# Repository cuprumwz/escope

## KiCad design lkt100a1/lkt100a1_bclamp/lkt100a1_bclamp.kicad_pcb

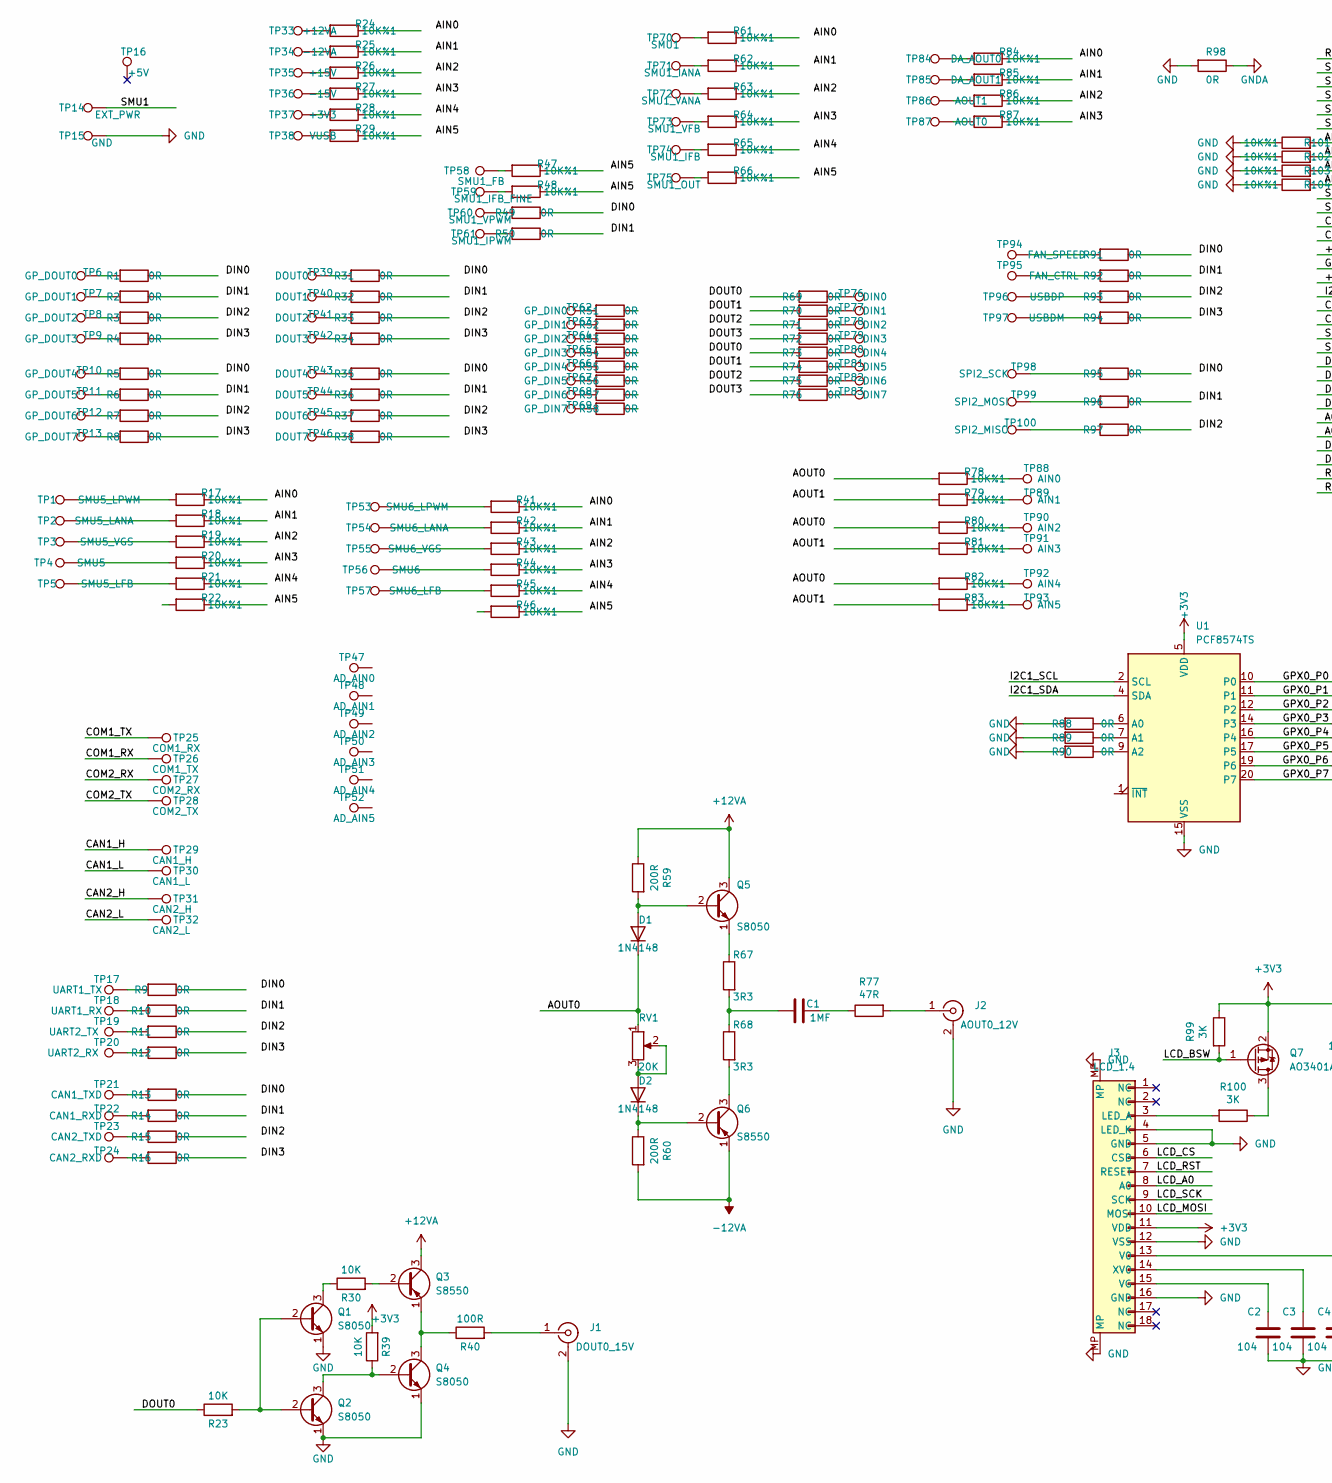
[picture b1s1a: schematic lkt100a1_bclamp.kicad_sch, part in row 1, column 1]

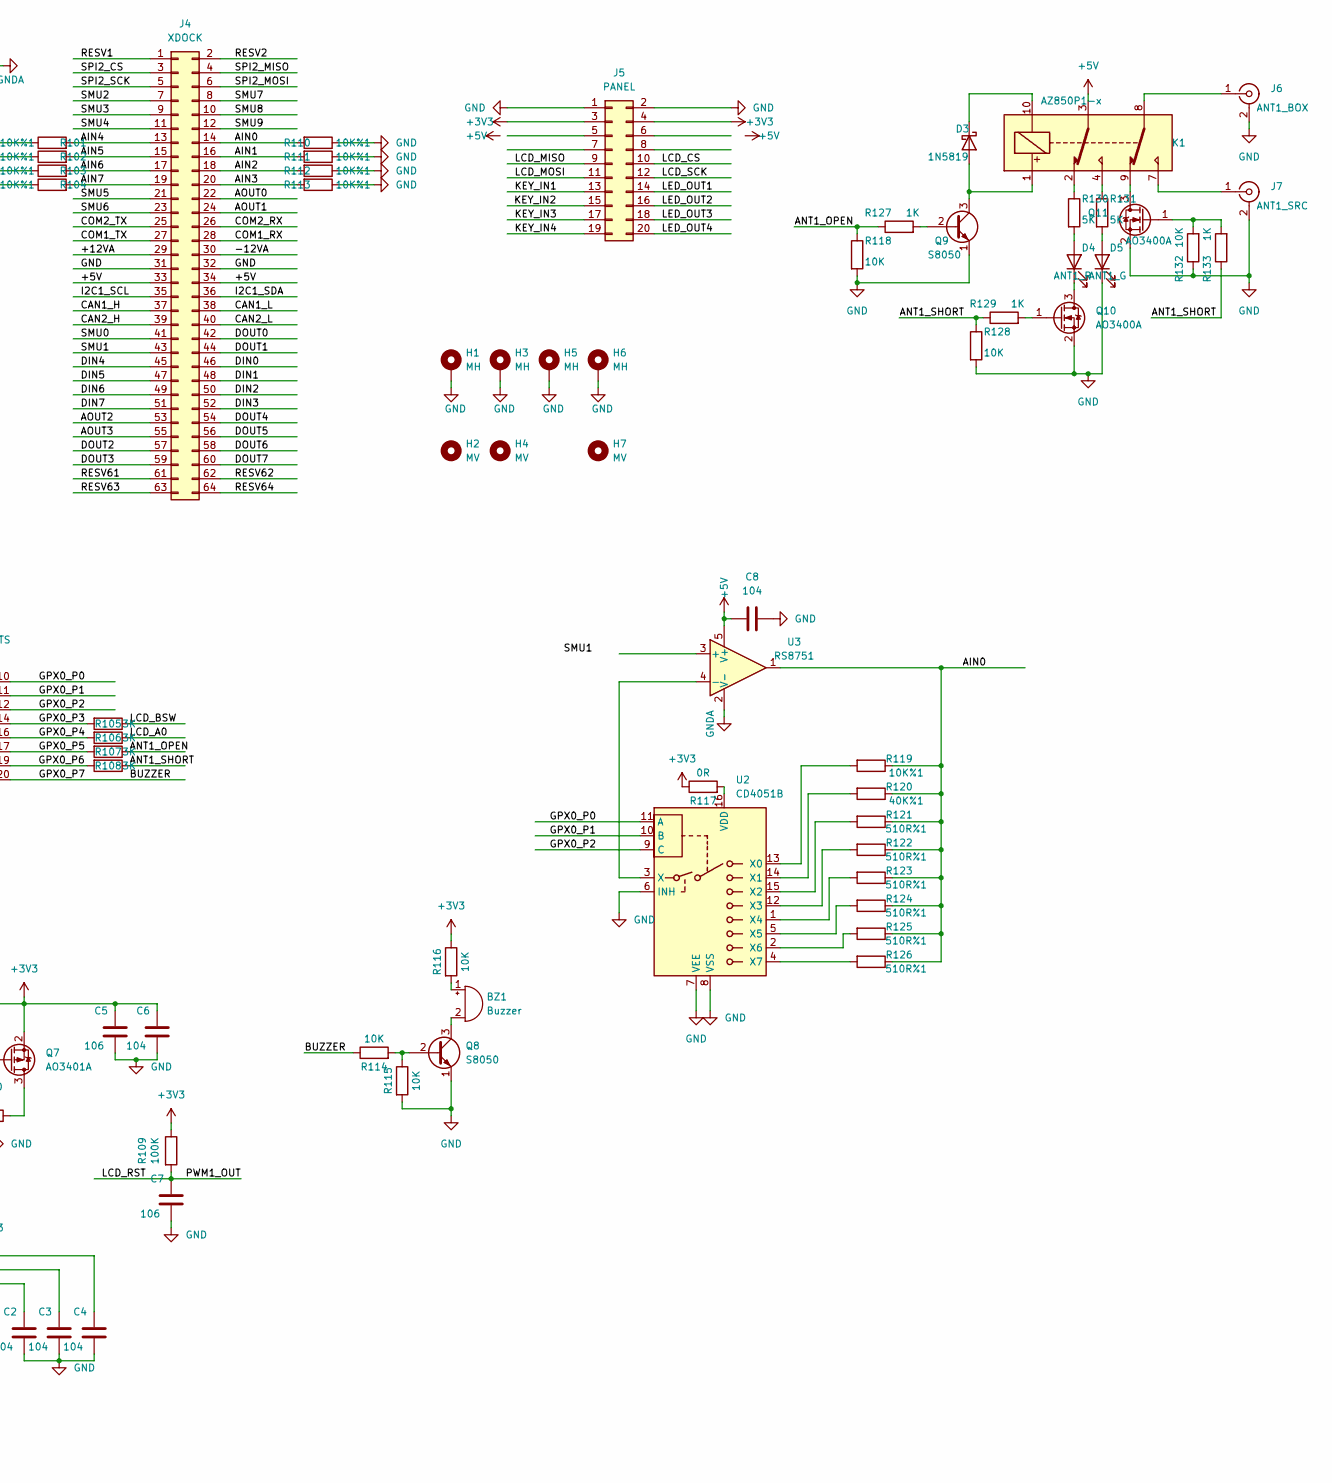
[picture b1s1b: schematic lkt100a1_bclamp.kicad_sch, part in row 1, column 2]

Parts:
BZ1: Buzzer; MagneticBuzzer_PUI_AT-0927-TT-6-R
C1: 1MF; C_0603_1608Metric
C2, C3, C4, C6, C8: 104; C_0603_1608Metric
C5: 106; C_0805_2012Metric
C7: 106; C_0603_1608Metric
D1, D2: 1N4148; D_0805_2012Metric
D3: 1N5819; D_1812_4532Metric
D4: ANT1_R; LED_0805_2012Metric
D5: ANT1_G; LED_0805_2012Metric
H1, H3, H5, H6: MH; MountingHole_2.7mm_M2.5_Pad_Via
H2, H4: MV; MountingHole_2.5mm
H7: MV; MountingHole_2.2mm_M2
J1: DOUT0_15V; SMA_Amphenol_901-143_Horizontal
J2: AOUT0_12V; SMA_Amphenol_901-143_Horizontal
J3: LCD_1.4; TE_1-84952-8_1x18-1MP_P1.0mm_Horizontal
J4: XDOCK; IDC-Header_2x32_P2.54mm_Horizontal
J5: PANEL; IDC-Header_2x10_P2.54mm_Horizontal
J6: ANT1_BOX; SMA_Amphenol_901-143_Horizontal
J7: ANT1_SRC; SMA_Amphenol_901-143_Horizontal
K1: AZ850P1-x; Relay_DPDT_FRT5_SMD
Q1, Q2, Q4, Q5, Q8, Q9: S8050; SOT-23
Q3, Q6: S8550; SOT-23
Q7: AO3401A; SOT-23
Q10, Q11: AO3400A; SOT-23
R1, R2, R3, R4, R5, R6, R7, R8, R9, R10, R11, R12, R13, R14, R15, R16, R31, R32, R33, R34, R35, R36, R37, R38, R49, R50, R51, R52, R53, R54, R55, R56, R57, R58, R69, R70, R71, R72, R73, R74, R75, R76, R88, R89, R90, R91, R92, R93, R94, R95, R96, R97, R98: 0R; R_0805_2012Metric
R17, R18, R19, R20, R21, R22, R24, R25, R26, R27, R28, R29, R41, R42, R43, R44, R45, R46, R47, R48, R61, R62, R63, R64, R65, R66, R78, R79, R80, R81, R82, R83, R84, R85, R86, R87, R101, R102, R103, R104, R110, R111, R112, R113, R119: 10K%1; R_0805_2012Metric
R23, R30, R39, R114, R115, R116, R118, R128, R132: 10K; R_0603_1608Metric
R40: 100R; R_0603_1608Metric
R59, R60: 200R; R_0603_1608Metric
R67, R68: 3R3; R_0603_1608Metric
R77: 47R; R_0603_1608Metric
R99, R100, R105, R106, R107, R108: 3K; R_0603_1608Metric
R109: 100K; R_0603_1608Metric
R117: 0R; R_0603_1608Metric
R120: 40K%1; R_0805_2012Metric
R121, R122, R123, R124, R125, R126: 510R%1; R_0805_2012Metric
R127, R129, R133: 1K; R_0603_1608Metric
R130, R131: 5K; R_0603_1608Metric
RV1: 20K; Potentiometer_Bourns_3296W_Vertical
TP1: SMU5_LPWM; TestPoint_THTPad_D1.5mm_Drill0.9mm
TP2: SMU5_LANA; TestPoint_THTPad_D1.5mm_Drill0.9mm
TP3: SMU5_VGS; TestPoint_THTPad_D1.5mm_Drill0.9mm
TP4: SMU5; TestPoint_THTPad_D1.5mm_Drill0.9mm
TP5: SMU5_LFB; TestPoint_THTPad_D1.5mm_Drill0.9mm
TP6: GP_DOUT0; TestPoint_THTPad_D1.5mm_Drill0.9mm
TP7: GP_DOUT1; TestPoint_THTPad_D1.5mm_Drill0.9mm
TP8: GP_DOUT2; TestPoint_THTPad_D1.5mm_Drill0.9mm
TP9: GP_DOUT3; TestPoint_THTPad_D1.5mm_Drill0.9mm
TP10: GP_DOUT4; TestPoint_THTPad_D1.5mm_Drill0.9mm
TP11: GP_DOUT5; TestPoint_THTPad_D1.5mm_Drill0.9mm
TP12: GP_DOUT6; TestPoint_THTPad_D1.5mm_Drill0.9mm
TP13: GP_DOUT7; TestPoint_THTPad_D1.5mm_Drill0.9mm
TP14: EXT_PWR; TestPoint_THTPad_D1.5mm_Drill0.9mm
TP15: GND; TestPoint_THTPad_D1.5mm_Drill0.9mm
TP16: +5V; TestPoint_THTPad_D1.5mm_Drill0.9mm
TP17: UART1_TX; TestPoint_THTPad_D1.5mm_Drill0.9mm
TP18: UART1_RX; TestPoint_THTPad_D1.5mm_Drill0.9mm
TP19: UART2_TX; TestPoint_THTPad_D1.5mm_Drill0.9mm
TP20: UART2_RX; TestPoint_THTPad_D1.5mm_Drill0.9mm
TP21: CAN1_TXD; TestPoint_THTPad_D1.5mm_Drill0.9mm
TP22: CAN1_RXD; TestPoint_THTPad_D1.5mm_Drill0.9mm
TP23: CAN2_TXD; TestPoint_THTPad_D1.5mm_Drill0.9mm
TP24: CAN2_RXD; TestPoint_THTPad_D1.5mm_Drill0.9mm
TP25: COM1_RX; TestPoint_THTPad_D1.5mm_Drill0.9mm
TP26: COM1_TX; TestPoint_THTPad_D1.5mm_Drill0.9mm
TP27: COM2_RX; TestPoint_THTPad_D1.5mm_Drill0.9mm
TP28: COM2_TX; TestPoint_THTPad_D1.5mm_Drill0.9mm
TP29: CAN1_H; TestPoint_THTPad_D1.5mm_Drill0.9mm
TP30: CAN1_L; TestPoint_THTPad_D1.5mm_Drill0.9mm
TP31: CAN2_H; TestPoint_THTPad_D1.5mm_Drill0.9mm
TP32: CAN2_L; TestPoint_THTPad_D1.5mm_Drill0.9mm
TP33: +12VA; TestPoint_THTPad_D1.5mm_Drill0.9mm
TP34: -12VA; TestPoint_THTPad_D1.5mm_Drill0.9mm
TP35: +15V; TestPoint_THTPad_D1.5mm_Drill0.9mm
TP36: -15V; TestPoint_THTPad_D1.5mm_Drill0.9mm
TP37: +3V3; TestPoint_THTPad_D1.5mm_Drill0.9mm
TP38: VUSB; TestPoint_THTPad_D1.5mm_Drill0.9mm
TP39: DOUT0; TestPoint_THTPad_D1.5mm_Drill0.9mm
TP40: DOUT1; TestPoint_THTPad_D1.5mm_Drill0.9mm
TP41: DOUT2; TestPoint_THTPad_D1.5mm_Drill0.9mm
TP42: DOUT3; TestPoint_THTPad_D1.5mm_Drill0.9mm
TP43: DOUT4; TestPoint_THTPad_D1.5mm_Drill0.9mm
TP44: DOUT5; TestPoint_THTPad_D1.5mm_Drill0.9mm
TP45: DOUT6; TestPoint_THTPad_D1.5mm_Drill0.9mm
TP46: DOUT7; TestPoint_THTPad_D1.5mm_Drill0.9mm
TP47: AD_AIN0; TestPoint_THTPad_D1.5mm_Drill0.9mm
TP48: AD_AIN1; TestPoint_THTPad_D1.5mm_Drill0.9mm
TP49: AD_AIN2; TestPoint_THTPad_D1.5mm_Drill0.9mm
TP50: AD_AIN3; TestPoint_THTPad_D1.5mm_Drill0.9mm
TP51: AD_AIN4; TestPoint_THTPad_D1.5mm_Drill0.9mm
TP52: AD_AIN5; TestPoint_THTPad_D1.5mm_Drill0.9mm
TP53: SMU6_LPWM; TestPoint_THTPad_D1.5mm_Drill0.9mm
TP54: SMU6_LANA; TestPoint_THTPad_D1.5mm_Drill0.9mm
TP55: SMU6_VGS; TestPoint_THTPad_D1.5mm_Drill0.9mm
TP56: SMU6; TestPoint_THTPad_D1.5mm_Drill0.9mm
TP57: SMU6_LFB; TestPoint_THTPad_D1.5mm_Drill0.9mm
TP58: SMU1_FB; TestPoint_THTPad_D1.5mm_Drill0.9mm
TP59: SMU1_IFB_FINE; TestPoint_THTPad_D1.5mm_Drill0.9mm
TP60: SMU1_VPWM; TestPoint_THTPad_D1.5mm_Drill0.9mm
TP61: SMU1_IPWM; TestPoint_THTPad_D1.5mm_Drill0.9mm
TP62: GP_DIN0; TestPoint_THTPad_D1.5mm_Drill0.9mm
TP63: GP_DIN1; TestPoint_THTPad_D1.5mm_Drill0.9mm
TP64: GP_DIN2; TestPoint_THTPad_D1.5mm_Drill0.9mm
TP65: GP_DIN3; TestPoint_THTPad_D1.5mm_Drill0.9mm
TP66: GP_DIN4; TestPoint_THTPad_D1.5mm_Drill0.9mm
TP67: GP_DIN5; TestPoint_THTPad_D1.5mm_Drill0.9mm
TP68: GP_DIN6; TestPoint_THTPad_D1.5mm_Drill0.9mm
TP69: GP_DIN7; TestPoint_THTPad_D1.5mm_Drill0.9mm
TP70: SMU1; TestPoint_THTPad_D1.5mm_Drill0.9mm
TP71: SMU1_IANA; TestPoint_THTPad_D1.5mm_Drill0.9mm
TP72: SMU1_VANA; TestPoint_THTPad_D1.5mm_Drill0.9mm
TP73: SMU1_VFB; TestPoint_THTPad_D1.5mm_Drill0.9mm
TP74: SMU1_IFB; TestPoint_THTPad_D1.5mm_Drill0.9mm
TP75: SMU1_OUT; TestPoint_THTPad_D1.5mm_Drill0.9mm
TP76: DIN0; TestPoint_THTPad_D1.5mm_Drill0.9mm
TP77: DIN1; TestPoint_THTPad_D1.5mm_Drill0.9mm
TP78: DIN2; TestPoint_THTPad_D1.5mm_Drill0.9mm
TP79: DIN3; TestPoint_THTPad_D1.5mm_Drill0.9mm
TP80: DIN4; TestPoint_THTPad_D1.5mm_Drill0.9mm
TP81: DIN5; TestPoint_THTPad_D1.5mm_Drill0.9mm
TP82: DIN6; TestPoint_THTPad_D1.5mm_Drill0.9mm
TP83: DIN7; TestPoint_THTPad_D1.5mm_Drill0.9mm
TP84: DA_AOUT0; TestPoint_THTPad_D1.5mm_Drill0.9mm
TP85: DA_AOUT1; TestPoint_THTPad_D1.5mm_Drill0.9mm
TP86: AOUT1; TestPoint_THTPad_D1.5mm_Drill0.9mm
TP87: AOUT0; TestPoint_THTPad_D1.5mm_Drill0.9mm
TP88: AIN0; TestPoint_THTPad_D1.5mm_Drill0.9mm
TP89: AIN1; TestPoint_THTPad_D1.5mm_Drill0.9mm
TP90: AIN2; TestPoint_THTPad_D1.5mm_Drill0.9mm
TP91: AIN3; TestPoint_THTPad_D1.5mm_Drill0.9mm
TP92: AIN4; TestPoint_THTPad_D1.5mm_Drill0.9mm
TP93: AIN5; TestPoint_THTPad_D1.5mm_Drill0.9mm
TP94: FAN_SPEED; TestPoint_THTPad_D1.5mm_Drill0.9mm
TP95: FAN_CTRL; TestPoint_THTPad_D1.5mm_Drill0.9mm
TP96: USBDP; TestPoint_THTPad_D1.5mm_Drill0.9mm
TP97: USBDM; TestPoint_THTPad_D1.5mm_Drill0.9mm
TP98: SPI2_SCK; TestPoint_THTPad_D1.5mm_Drill0.9mm
TP99: SPI2_MOSI; TestPoint_THTPad_D1.5mm_Drill0.9mm
TP100: SPI2_MISO; TestPoint_THTPad_D1.5mm_Drill0.9mm
U1: PCF8574TS; SSOP-20_4.4x6.5mm_P0.65mm
U2: CD4051B; TSSOP-16_4.4x5mm_P0.65mm
U3: RS8751; SOT-23-5

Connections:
+3V3: C5.1, C6.1, J3.11 (VDD), J5.3, J5.4, Q7.2 (S), R39.2, R99.1, R109.1, R116.1, R117.1, U1.5 (VDD)
+5V: C8.2, J4.33, J4.34, K1.3, U3.5 (V+)
+12VA: J4.29, Q3.3 (C), Q5.3 (C), R59.1
-12VA: J4.30, Q6.1 (E), R60.2
/AIN0: J4.14, R110.2, R119.1, R120.1, R121.1, R122.1, R123.1, R124.1, R125.1, R126.1, U3.1
/AIN1: J4.16, R111.2
/AIN2: J4.18, R112.2
/AIN3: J4.20, R113.2
/AIN4: J4.13, R101.2
/AIN5: J4.15, R102.2
/AIN6: J4.17, R103.2
/AIN7: J4.19, R104.2
/ANT1_OPEN: R107.1, R118.1, R127.1
/ANT1_SHORT: R108.1, R128.1, R129.1, R133.1
/AOUT0: D1.1 (K), J4.22, RV1.1
/AOUT1: J4.24
/AOUT2: J4.53
/AOUT3: J4.55
/BUZZER: R114.1, U1.20 (P7)
/CAN1_H: J4.37, TP29.1
/CAN1_L: J4.38, TP30.1
/CAN2_H: J4.39, TP31.1
/CAN2_L: J4.40, TP32.1
/COM1_RX: J4.28, TP26.1
/COM1_TX: J4.27, TP25.1
/COM2_RX: J4.26, TP27.1
/COM2_TX: J4.25, TP28.1
/DIN0: J4.46
/DIN1: J4.48
/DIN2: J4.50
/DIN3: J4.52
/DIN4: J4.45
/DIN5: J4.47
/DIN6: J4.49
/DIN7: J4.51
/DOUT0: J4.42, R23.1
/DOUT1: J4.44
/DOUT2: J4.57
/DOUT3: J4.59
/DOUT4: J4.54
/DOUT5: J4.56
/DOUT6: J4.58
/DOUT7: J4.60
/GPX0_P0: U1.10 (P0), U2.11 (A)
/GPX0_P1: U1.11 (P1), U2.10 (B)
/GPX0_P2: U1.12 (P2), U2.9 (C)
/GPX0_P3: R105.2, U1.14 (P3)
/GPX0_P4: R106.2, U1.16 (P4)
/GPX0_P5: R107.2, U1.17 (P5)
/GPX0_P6: R108.2, U1.19 (P6)
/I2C1_SCL: J4.35, U1.2 (SCL)
/I2C1_SDA: J4.36, U1.4 (SDA)
/KEY_IN1: J5.13
/KEY_IN2: J5.15
/KEY_IN3: J5.17
/KEY_IN4: J5.19
/LCD_A0: J3.8 (A0), R106.1
/LCD_BSW: Q7.1 (G), R99.2, R105.1
/LCD_CS: J3.6 (CSB), J5.10
/LCD_MISO: J5.9
/LCD_MOSI: J3.10 (MOSI), J5.11
/LCD_RST: C7.1, J3.7 (RESET), R109.2
/LCD_SCK: J3.9 (SCK), J5.12
/LED_OUT1: J5.14
/LED_OUT2: J5.16
/LED_OUT3: J5.18
/LED_OUT4: J5.20
/RESV1: J4.1
/RESV2: J4.2
/RESV61: J4.61
/RESV62: J4.62
/RESV63: J4.63
/RESV64: J4.64
/SMU0: J4.41
/SMU1: J4.43, TP14.1
/SMU2: J4.7
/SMU3: J4.9
/SMU4: J4.11
/SMU5: J4.21
/SMU6: J4.23
/SMU7: J4.8
/SMU8: J4.10
/SMU9: J4.12
/SPI2_CS: J4.3
/SPI2_MISO: J4.4
/SPI2_MOSI: J4.6
/SPI2_SCK: J4.5
GND: C2.2, C3.2, C4.2, C5.2, C6.2, C7.2, C8.1, D5.1 (K), H1.1, H3.1, H5.1, H6.1, J1.2 (Ext), J2.2 (Ext), J3.4 (LED_K), J3.5 (GND), J3.12 (VSS), J3.16 (GND), J3.MP, J4.31, J4.32, J5.1, J5.2, J6.2 (Ext), J7.2 (Ext), Q1.1 (E), Q2.1 (E), Q4.1 (E), Q8.1 (E), Q9.1 (E), Q10.2 (S), Q11.2 (S), R88.2, R89.2, R90.2, R98.2, R101.1, R102.1, R103.1, R104.1, R110.1, R111.1, R112.1, R113.1, R115.2, R118.2, R128.2, R132.1, TP15.1, U1.15 (VSS), U2.6 (INH), U2.7 (VEE), U2.8 (VSS)
GNDA: R98.1, U3.2 (V-)
unnamed: BZ1.1 (-), R116.2
unnamed: BZ1.2 (+), Q8.3 (C)
unnamed: C1.1, R77.1
unnamed: C1.2, R67.2, R68.1
unnamed: C2.1, J3.15 (VG)
unnamed: C3.1, J3.14 (XV0)
unnamed: C4.1, J3.13 (V0)
unnamed: D1.2 (A), Q5.2 (B), R59.2
unnamed: D2.1 (K), Q6.2 (B), R60.1
unnamed: D2.2 (A), RV1.2, RV1.3
unnamed: D3.1 (K), K1.10
unnamed: D3.2 (A), K1.1, Q9.3 (C)
unnamed: D4.1 (K), Q10.3 (D)
unnamed: D4.2 (A), R130.2
unnamed: D5.2 (A), R131.2
unnamed: J1.1 (In), R40.2
unnamed: J2.1 (In), R77.2
unnamed: J3.3 (LED_A), R100.2
unnamed: J6.1 (In), K1.8
unnamed: J7.1 (In), K1.7
unnamed: K1.2, R130.1
unnamed: K1.4, R131.1
unnamed: K1.9, Q11.3 (D)
unnamed: Q1.2 (B), Q2.2 (B), R23.2
unnamed: Q1.3 (C), R30.1
unnamed: Q2.3 (C), Q4.2 (B), R39.1
unnamed: Q3.1 (E), Q4.3 (C), R40.1
unnamed: Q3.2 (B), R30.2
unnamed: Q5.1 (E), R67.1
unnamed: Q6.3 (C), R68.2
unnamed: Q7.3 (D), R100.1
unnamed: Q8.2 (B), R114.2, R115.1
unnamed: Q9.2 (B), R127.2
unnamed: Q10.1 (G), R129.2
unnamed: Q11.1 (G), R132.2, R133.2
unnamed: R1.2, TP6.1
unnamed: R2.2, TP7.1
unnamed: R3.2, TP8.1
unnamed: R4.2, TP9.1
unnamed: R5.2, TP10.1
unnamed: R6.2, TP11.1
unnamed: R7.2, TP12.1
unnamed: R8.2, TP13.1
unnamed: R9.2, TP17.1
unnamed: R10.2, TP18.1
unnamed: R11.2, TP19.1
unnamed: R12.2, TP20.1
unnamed: R13.2, TP21.1
unnamed: R14.2, TP22.1
unnamed: R15.2, TP23.1
unnamed: R16.2, TP24.1
unnamed: R17.2, TP1.1
unnamed: R18.2, TP2.1
unnamed: R19.2, TP3.1
unnamed: R20.2, TP4.1
unnamed: R21.2, TP5.1
unnamed: R24.2, TP33.1
unnamed: R25.2, TP34.1
unnamed: R26.2, TP35.1
unnamed: R27.2, TP36.1
unnamed: R28.2, TP37.1
unnamed: R29.2, TP38.1
unnamed: R31.2, TP39.1
unnamed: R32.2, TP40.1
unnamed: R33.2, TP41.1
unnamed: R34.2, TP42.1
unnamed: R35.2, TP43.1
unnamed: R36.2, TP44.1
unnamed: R37.2, TP45.1
unnamed: R38.2, TP46.1
unnamed: R41.2, TP53.1
unnamed: R42.2, TP54.1
unnamed: R43.2, TP55.1
unnamed: R44.2, TP56.1
unnamed: R45.2, TP57.1
unnamed: R47.2, TP58.1
unnamed: R48.2, TP59.1
unnamed: R49.2, TP60.1
unnamed: R50.2, TP61.1
unnamed: R51.2, TP62.1
unnamed: R52.2, TP63.1
unnamed: R53.2, TP64.1
unnamed: R54.2, TP65.1
unnamed: R55.2, TP66.1
unnamed: R56.2, TP67.1
unnamed: R57.2, TP68.1
unnamed: R58.2, TP69.1
unnamed: R61.2, TP70.1
unnamed: R62.2, TP71.1
unnamed: R63.2, TP72.1
unnamed: R64.2, TP73.1
unnamed: R65.2, TP74.1
unnamed: R66.2, TP75.1
unnamed: R69.1, TP76.1
unnamed: R70.1, TP77.1
unnamed: R71.1, TP78.1
unnamed: R72.1, TP79.1
unnamed: R73.1, TP80.1
unnamed: R74.1, TP81.1
unnamed: R75.1, TP82.1
unnamed: R76.1, TP83.1
unnamed: R78.1, TP88.1
unnamed: R79.1, TP89.1
unnamed: R80.1, TP90.1
unnamed: R81.1, TP91.1
unnamed: R82.1, TP92.1
unnamed: R83.1, TP93.1
unnamed: R84.2, TP84.1
unnamed: R85.2, TP85.1
unnamed: R86.2, TP86.1
unnamed: R87.2, TP87.1
unnamed: R88.1, U1.6 (A0)
unnamed: R89.1, U1.7 (A1)
unnamed: R90.1, U1.9 (A2)
unnamed: R91.2, TP94.1
unnamed: R92.2, TP95.1
unnamed: R93.2, TP96.1
unnamed: R94.2, TP97.1
unnamed: R95.2, TP98.1
unnamed: R96.2, TP99.1
unnamed: R97.2, TP100.1
unnamed: R117.2, U2.16 (VDD)
unnamed: R119.2, U2.13 (X0)
unnamed: R120.2, U2.14 (X1)
unnamed: R121.2, U2.15 (X2)
unnamed: R122.2, U2.12 (X3)
unnamed: R123.2, U2.1 (X4)
unnamed: R124.2, U2.5 (X5)
unnamed: R125.2, U2.2 (X6)
unnamed: R126.2, U2.4 (X7)
unnamed: U2.3 (X), U3.4 (-)

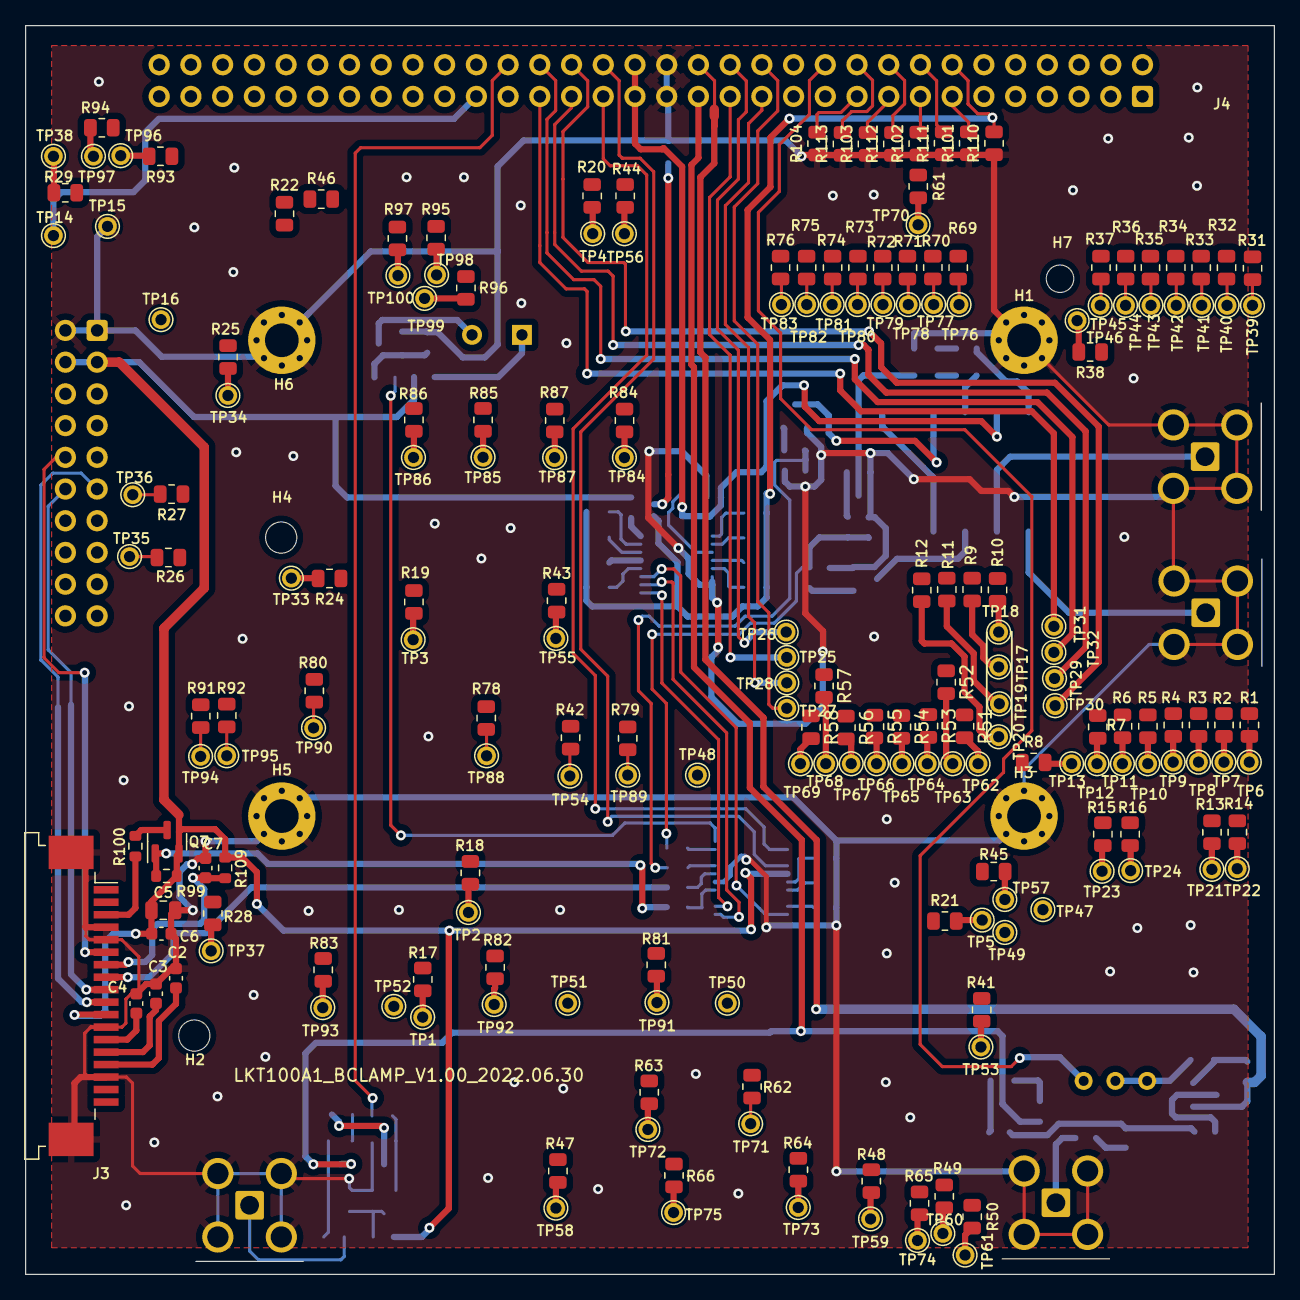
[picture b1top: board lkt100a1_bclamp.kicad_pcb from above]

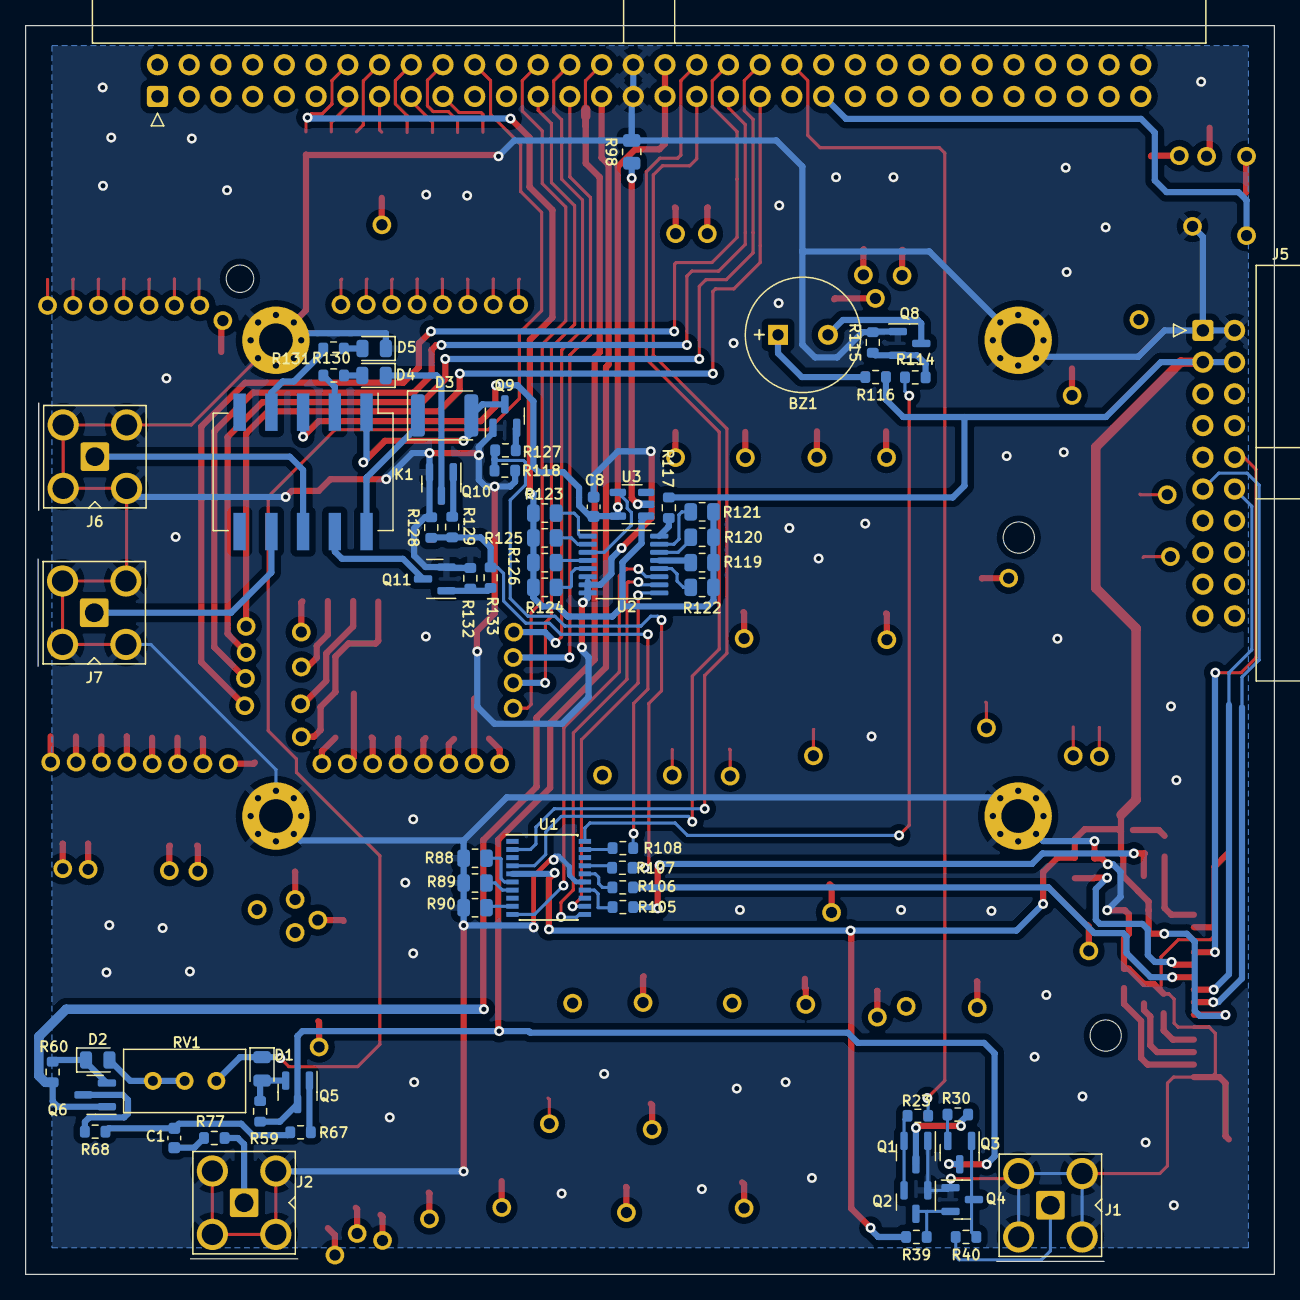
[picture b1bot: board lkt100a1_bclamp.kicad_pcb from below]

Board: 2 copper layers, 100.0 x 100.0 mm, 277 parts (66 on the bottom side), 174 nets.
